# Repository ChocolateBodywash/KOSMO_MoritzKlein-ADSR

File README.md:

## KOSMO Format Moritz Klein ADSR

A KOSMO format of Moritz Klein’s ADSR

This should have been my first dip into PCB design but it was my second. It's a pretty straight forward design.

---
Note: This was created by a hobbyist with no formal engineering training outside various late night YouTube binges. 
I’ve confirmed these designs to work but I make no guarantees on the design working efficiently.. or working at all.

Additional credit: Analog Output (Richard Holmes) for footprint libraries and front panel templates.

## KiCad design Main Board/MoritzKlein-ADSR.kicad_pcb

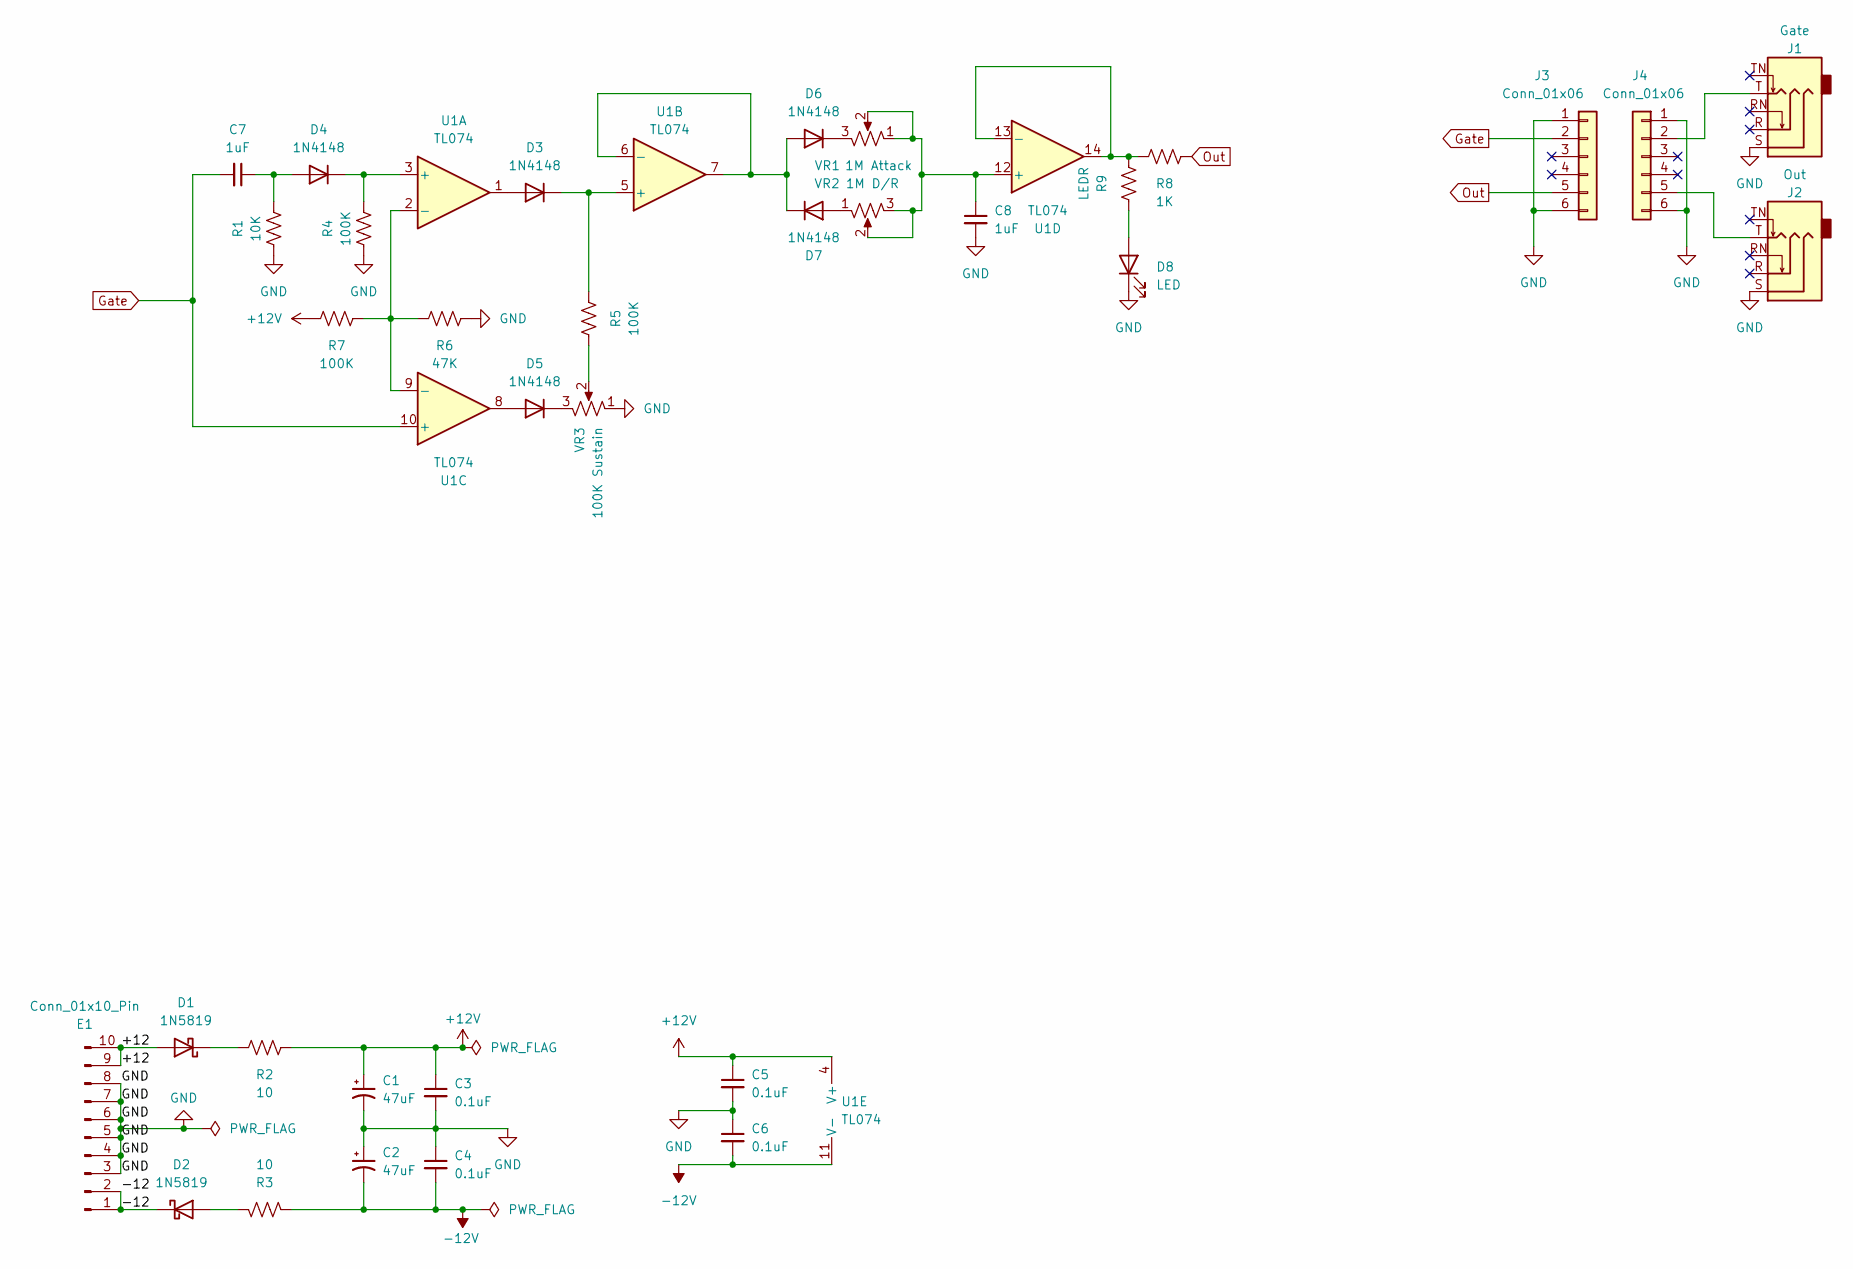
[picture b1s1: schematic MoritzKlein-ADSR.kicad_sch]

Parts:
C1, C2: 47uF; CP_Radial_D5.0mm_P2.50mm
C3, C4, C5, C6: 0.1uF; C_Disc_D3.0mm_W1.6mm_P2.50mm
C7, C8: 1uF; C_Rect_L7.2mm_W2.5mm_P5.00mm_FKS2_FKP2_MKS2_MKP2
D1, D2: 1N5819; D_DO-41_SOD81_P10.16mm_Horizontal
D3, D4, D5, D6, D7: 1N4148; D_DO-35_SOD27_P7.62mm_Horizontal
D8: LED; LED_D5.0mm
E1: Conn_01x10_Pin; Pins_2x05_2.54mm_TH_EurorackPower_Shrouded
J1: Gate; Jack_6.35mm_PJ_629HAN
J2: Out; Jack_6.35mm_PJ_629HAN
J3, J4: Conn_01x06; PinHeader_1x06_P2.54mm_Vertical
R1: 10K; R_Axial_DIN0207_L6.3mm_D2.5mm_P10.16mm_Horizontal
R2, R3: 10; R_Axial_DIN0207_L6.3mm_D2.5mm_P10.16mm_Horizontal
R4, R5, R7: 100K; R_Axial_DIN0207_L6.3mm_D2.5mm_P10.16mm_Horizontal
R6: 47K; R_Axial_DIN0207_L6.3mm_D2.5mm_P10.16mm_Horizontal
R8: 1K; R_Axial_DIN0207_L6.3mm_D2.5mm_P10.16mm_Horizontal
R9: LEDR; R_Axial_DIN0207_L6.3mm_D2.5mm_P10.16mm_Horizontal
U1: TL074; DIP-14_W7.62mm
VR1: 1M Attack; Potentiometer_Alpha_RD901F-40-00D_Single_Vertical
VR2: 1M D/R; Potentiometer_Alpha_RD901F-40-00D_Single_Vertical
VR3: 100K Sustain; Potentiometer_Alpha_RD901F-40-00D_Single_Vertical

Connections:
+12V: C1.1, C3.1, C5.1, R2.2, R7.1, U1.4 (V+)
-12V: C2.2, C4.2, C6.2, R3.2, U1.11 (V-)
/+12: D1.2 (A), E1.9, E1.10
/-12: D2.1 (K), E1.1, E1.2
GND: C1.2, C2.1, C3.2, C4.1, C5.2, C6.1, C8.2, D8.1 (K), E1.3, E1.4, E1.5, E1.6, E1.7, E1.8, J1.S, J2.S, J3.1, J3.6, J4.1, J4.6, R1.1, R4.1, R6.2, VR3.1
Gate: C7.2, J3.2, U1.10 (+)
unnamed: D1.1 (K), R2.1
unnamed: D2.2 (A), R3.1
unnamed: D3.2 (A), U1.1
unnamed: D3.1 (K), R5.2, U1.5 (+)
unnamed: C7.1, D4.2 (A), R1.2
unnamed: D4.1 (K), R4.2, U1.3 (+)
unnamed: D5.2 (A), U1.8
unnamed: D5.1 (K), VR3.3
unnamed: D6.2 (A), D7.1 (K), U1.6 (-), U1.7
unnamed: D6.1 (K), VR1.3
unnamed: D7.2 (A), VR2.1
unnamed: D8.2 (A), R9.2
unnamed: J1.T, J4.2
unnamed: J2.T, J4.5
unnamed: R5.1, VR3.2
unnamed: R6.1, R7.2, U1.2 (-), U1.9 (-)
unnamed: C8.1, U1.12 (+), VR1.1, VR1.2, VR2.2, VR2.3
unnamed: R8.1, R9.1, U1.13 (-), U1.14
Out: J3.5, R8.2

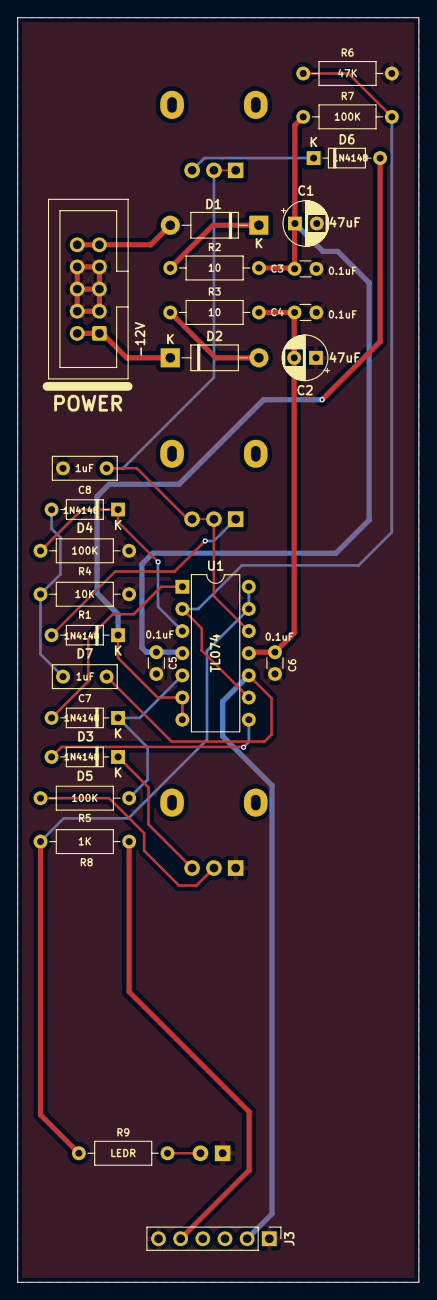
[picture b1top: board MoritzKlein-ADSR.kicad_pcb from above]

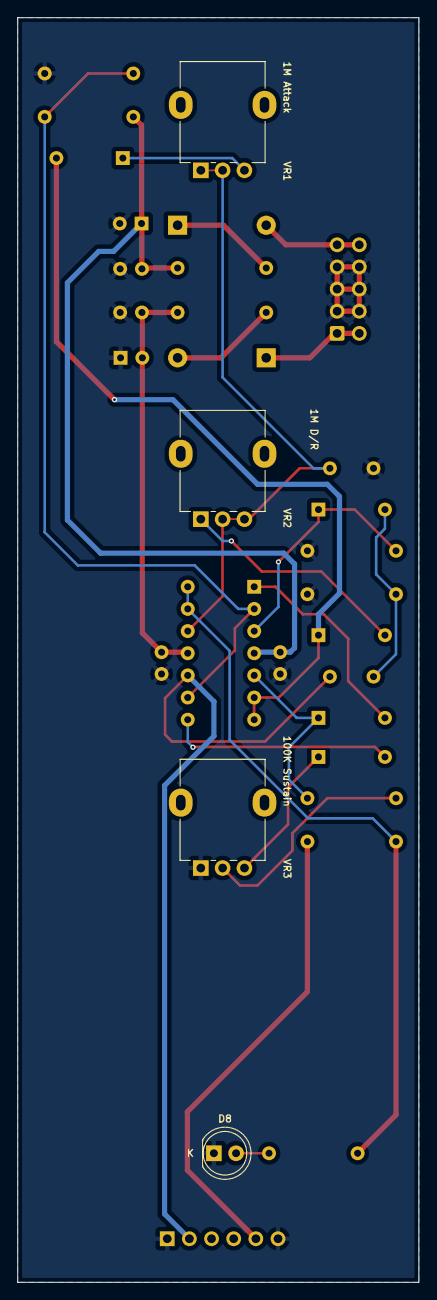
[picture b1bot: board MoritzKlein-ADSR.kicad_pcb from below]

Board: 2 copper layers, 46.0 x 145.0 mm, 31 parts (4 on the bottom side), 23 nets.

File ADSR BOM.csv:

Reference,Value,Datasheet,Package,Qty
"C1,C2",47uF,~,Electrolytic Capacitor,2
"C3,C4,C5,C6",0.1uF,~,Ceramic Disc Capacitor,4
"C7,C8",1uF,~,Box Style Film Capacitor,2
"D1,D2",1N5819,http://www.vishay.com/docs/88525/1n5817.pdf,Diode_THT:D_DO-41_SOD81_P10.16mm_Horizontal,2
"D3,D4,D5,D6,D7",1N4148,https://assets.nexperia.com/documents/data-sheet/1N4148_1N4448.pdf,Diode_THT:D_DO-35_SOD27_P7.62mm_Horizontal,5
D8,LED,~,LED 5.0mm,1
E1,Conn_02x05_Pin,~,Pins_2x05_2.54mm_TH_EurorackPower_Shrouded,1
J1,Gate,~,Jack_6.35mm,1
J2,Out,~,Jack_6.35mm,1
"J3,J4",Conn_01x06,~,Connector_PinHeader_2.54mm:PinHeader_1x06_P2.54mm_Vertical,2
R1,10K,~,Metal Film 1/4 Resistor,1
"R2,R3",10,~,Metal Film 1/4 Resistor,2
"R4,R5,R7",100K,~,Metal Film 1/4 Resistor,3
R6,47K,~,Metal Film 1/4 Resistor,1
R8,1K,~,Metal Film 1/4 Resistor,1
R9,LEDR,~,Metal Film 1/4 Resistor,1
U1,TL074,http://www.ti.com/lit/ds/symlink/tl071.pdf,DIP-14_W7.62mm,1
VR1,1M Attack,~,Potentiometer_Alpha_RD901F-40-00D_Single_Vertical,1
VR2,1M D/R,~,Potentiometer_Alpha_RD901F-40-00D_Single_Vertical,1
VR3,100K Sustain,~,Potentiometer_Alpha_RD901F-40-00D_Single_Vertical,1

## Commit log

2025-10-24 Upload files
2025-10-27 Update image
2025-10-29 Upload Schematics
